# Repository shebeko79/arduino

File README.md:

## Projects description
[Pulmonary Function Testing (PFT)](./pft)

[Car track using telegram bot](./car_dfrobot)

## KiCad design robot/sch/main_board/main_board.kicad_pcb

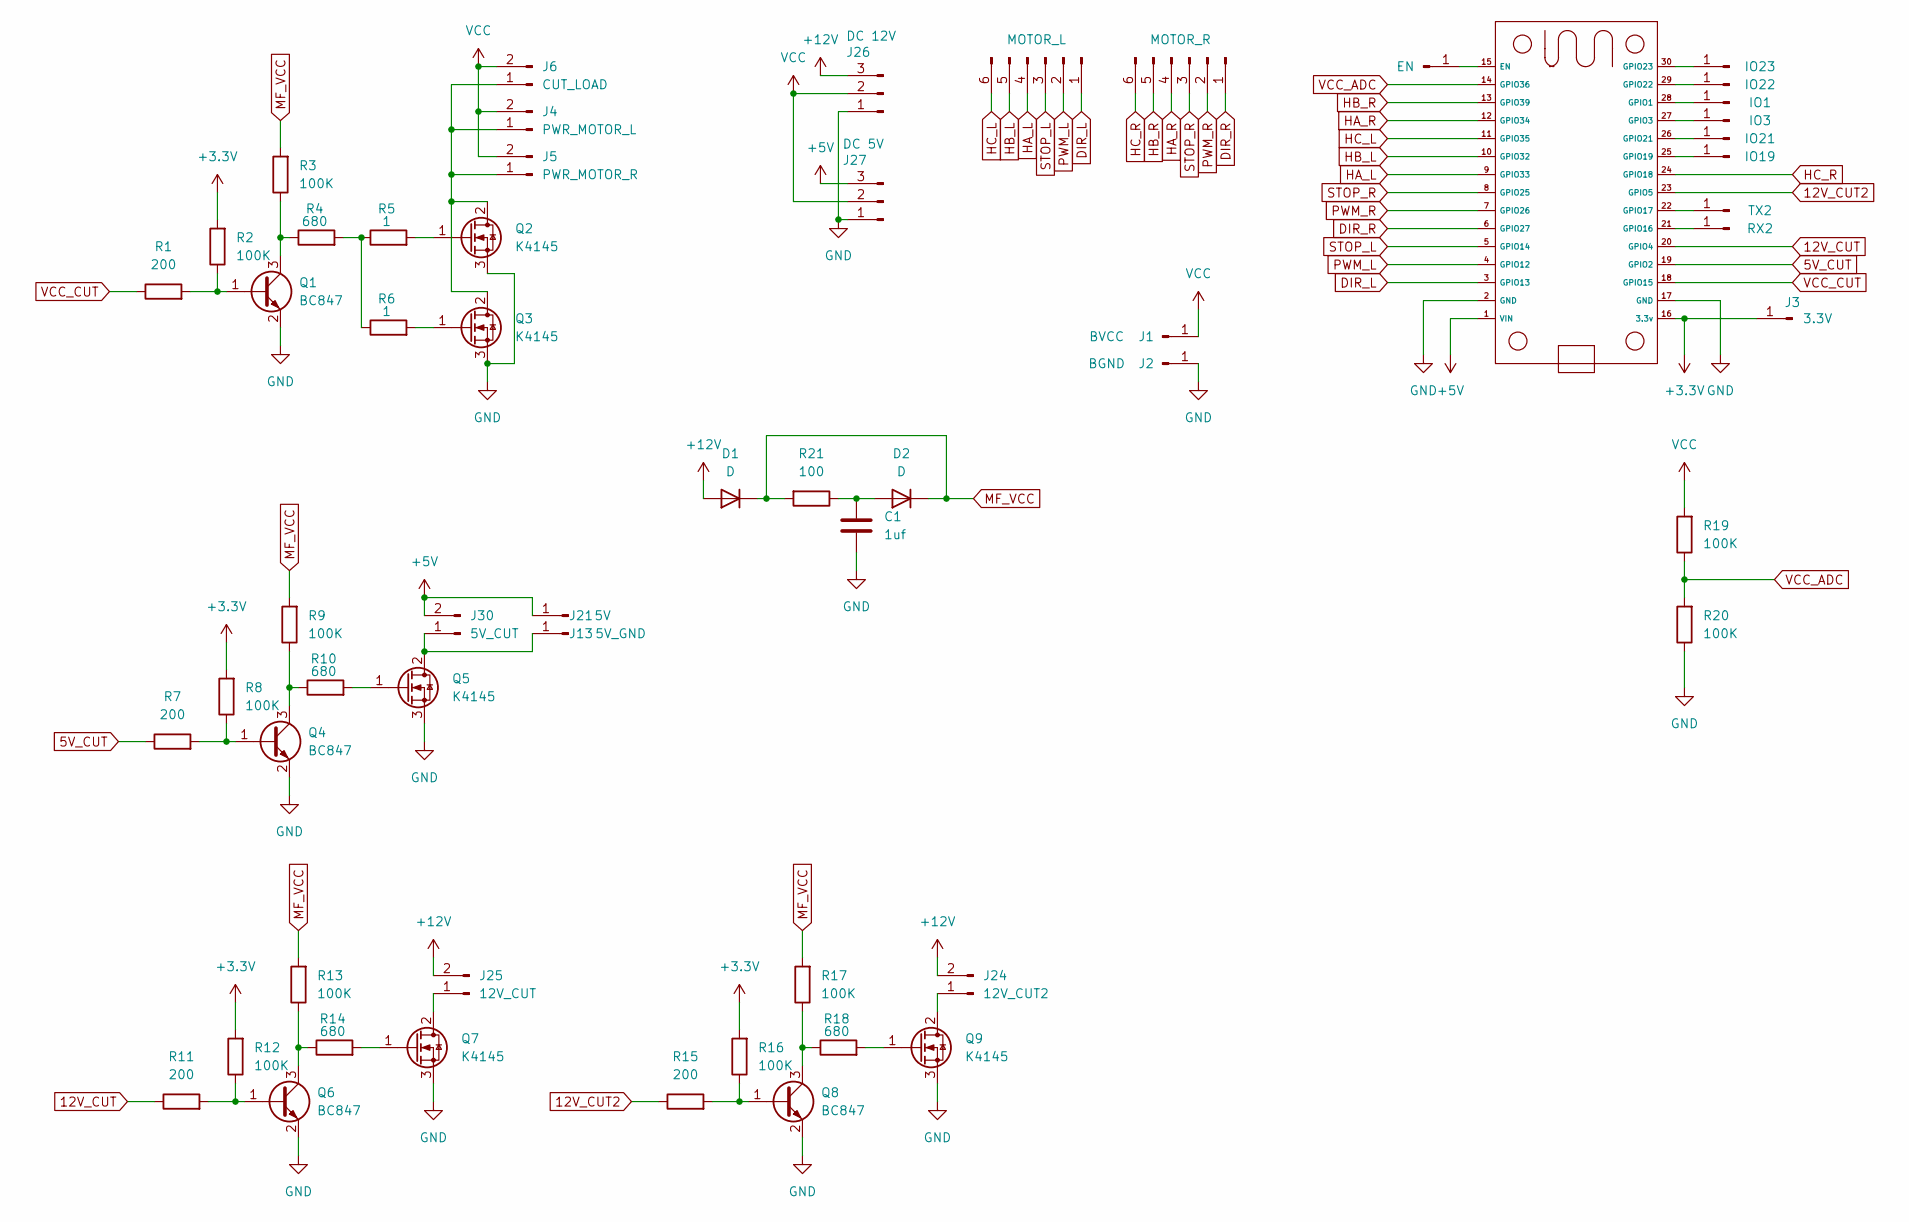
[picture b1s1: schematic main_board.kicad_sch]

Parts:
C1: 1uf; C_0805_2012Metric_Pad1.18x1.45mm_HandSolder
D1, D2: D; D_SMA_Handsoldering
J1: BVCC; SolderWirePad_1x01_SMD_4x8mm
J2: BGND; SolderWirePad_1x01_SMD_4x8mm
J3: 3.3V; SolderWirePad_1x01_SMD_2x4mm
J4: PWR_MOTOR_L; SolderWire-2.5sqmm_1x02_P7.2mm_D2.4mm_OD3.6mm
J5: PWR_MOTOR_R; SolderWire-2.5sqmm_1x02_P7.2mm_D2.4mm_OD3.6mm
J6: CUT_LOAD; SolderWire-2.5sqmm_1x02_P7.2mm_D2.4mm_OD3.6mm
J7: MOTOR_L; JST_XH_B6B-XH-A_1x06_P2.50mm_Vertical
J8: MOTOR_R; JST_XH_B6B-XH-A_1x06_P2.50mm_Vertical
J9: EN; SolderWirePad_1x01_SMD_1.5x3mm
J13: 5V_GND; SolderWirePad_1x01_SMD_2x4mm
J14: IO23; SolderWirePad_1x01_SMD_1.5x3mm
J15: IO22; SolderWirePad_1x01_SMD_1.5x3mm
J16: IO1; SolderWirePad_1x01_SMD_1.5x3mm
J17: IO3; SolderWirePad_1x01_SMD_1.5x3mm
J18: IO21; SolderWirePad_1x01_SMD_1.5x3mm
J19: IO19; SolderWirePad_1x01_SMD_1.5x3mm
J21: 5V; SolderWirePad_1x01_SMD_2x4mm
J22: TX2; SolderWirePad_1x01_SMD_1.5x3mm
J23: RX2; SolderWirePad_1x01_SMD_1.5x3mm
J24: 12V_CUT2; SolderWire-1sqmm_1x02_P5.4mm_D1.4mm_OD2.7mm
J25: 12V_CUT; SolderWire-1sqmm_1x02_P5.4mm_D1.4mm_OD2.7mm
J26: DC 12V; SolderWire-1.5sqmm_1x03_P6mm_D1.7mm_OD3mm
J27: DC 5V; SolderWire-1.5sqmm_1x03_P6mm_D1.7mm_OD3mm
J30: 5V_CUT; SolderWire-1sqmm_1x02_P5.4mm_D1.4mm_OD2.7mm
Q1, Q4, Q6, Q8: BC847; SOT-23
Q2, Q3, Q5, Q7, Q9: K4145; TO-220-3_Vertical
R1, R7, R11, R15: 200; R_0805_2012Metric
R2, R3, R8, R9, R12, R13, R16, R17, R19, R20: 100K; R_0805_2012Metric
R4, R10, R14, R18: 680; R_0805_2012Metric
R5, R6: 1; R_0805_2012Metric
R21: 100; R_0805_2012Metric
U1: ESP32_30pin

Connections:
5V_CUT: R7.1, U1.19 (GPIO2)
12V_CUT: R11.1, U1.20 (GPIO4)
12V_CUT2: R15.1, U1.23 (GPIO5)
+3.3V: J3.1, R2.2, R8.2, R12.2, R16.2, U1.16 (3.3v)
+5V: J21.1, J27.3, J30.2, U1.1 (VIN)
+12V: D1.2 (A), J24.2, J25.2, J26.3
DIR_L: J7.1, U1.3 (GPIO13)
DIR_R: J8.1, U1.6 (GPIO27)
GND: C1.1, J2.1, J26.1, J27.1, Q1.2 (E), Q2.3 (S), Q3.3 (S), Q4.2 (E), Q5.3 (S), Q6.2 (E), Q7.3 (S), Q8.2 (E), Q9.3 (S), R20.1, U1.2 (GND), U1.17 (GND)
HA_L: J7.4, U1.9 (GPIO33)
HA_R: J8.4, U1.12 (GPIO34)
HB_L: J7.5, U1.10 (GPIO32)
HB_R: J8.5, U1.13 (GPIO39)
HC_L: J7.6, U1.11 (GPIO35)
HC_R: J8.6, U1.24 (GPIO18)
MF_VCC: D1.1 (K), D2.1 (K), R3.2, R9.2, R13.2, R17.2, R21.2
unnamed: C1.2, D2.2 (A), R21.1
unnamed: J4.1, J5.1, J6.1, Q2.2 (D), Q3.2 (D)
unnamed: J9.1, U1.15 (EN)
unnamed: J13.1, J30.1, Q5.2 (D)
unnamed: J14.1, U1.30 (GPIO23)
unnamed: J15.1, U1.29 (GPIO22)
unnamed: J16.1, U1.28 (GPIO1)
unnamed: J17.1, U1.27 (GPIO3)
unnamed: J18.1, U1.26 (GPIO21)
unnamed: J19.1, U1.25 (GPIO19)
unnamed: J22.1, U1.22 (GPIO17)
unnamed: J23.1, U1.21 (GPIO16)
unnamed: J24.1, Q9.2 (D)
unnamed: J25.1, Q7.2 (D)
unnamed: Q1.1 (B), R1.2, R2.1
unnamed: Q1.3 (C), R3.1, R4.1
unnamed: Q2.1 (G), R5.2
unnamed: Q3.1 (G), R6.2
unnamed: Q4.1 (B), R7.2, R8.1
unnamed: Q4.3 (C), R9.1, R10.1
unnamed: Q5.1 (G), R10.2
unnamed: Q6.1 (B), R11.2, R12.1
unnamed: Q6.3 (C), R13.1, R14.1
unnamed: Q7.1 (G), R14.2
unnamed: Q8.1 (B), R15.2, R16.1
unnamed: Q8.3 (C), R17.1, R18.1
unnamed: Q9.1 (G), R18.2
unnamed: R4.2, R5.1, R6.1
PWM_L: J7.2, U1.4 (GPIO12)
PWM_R: J8.2, U1.7 (GPIO26)
STOP_L: J7.3, U1.5 (GPIO14)
STOP_R: J8.3, U1.8 (GPIO25)
VCC: J1.1, J4.2, J5.2, J6.2, J26.2, J27.2, R19.2
VCC_ADC: R19.1, R20.2, U1.14 (GPIO36)
VCC_CUT: R1.1, U1.18 (GPIO15)

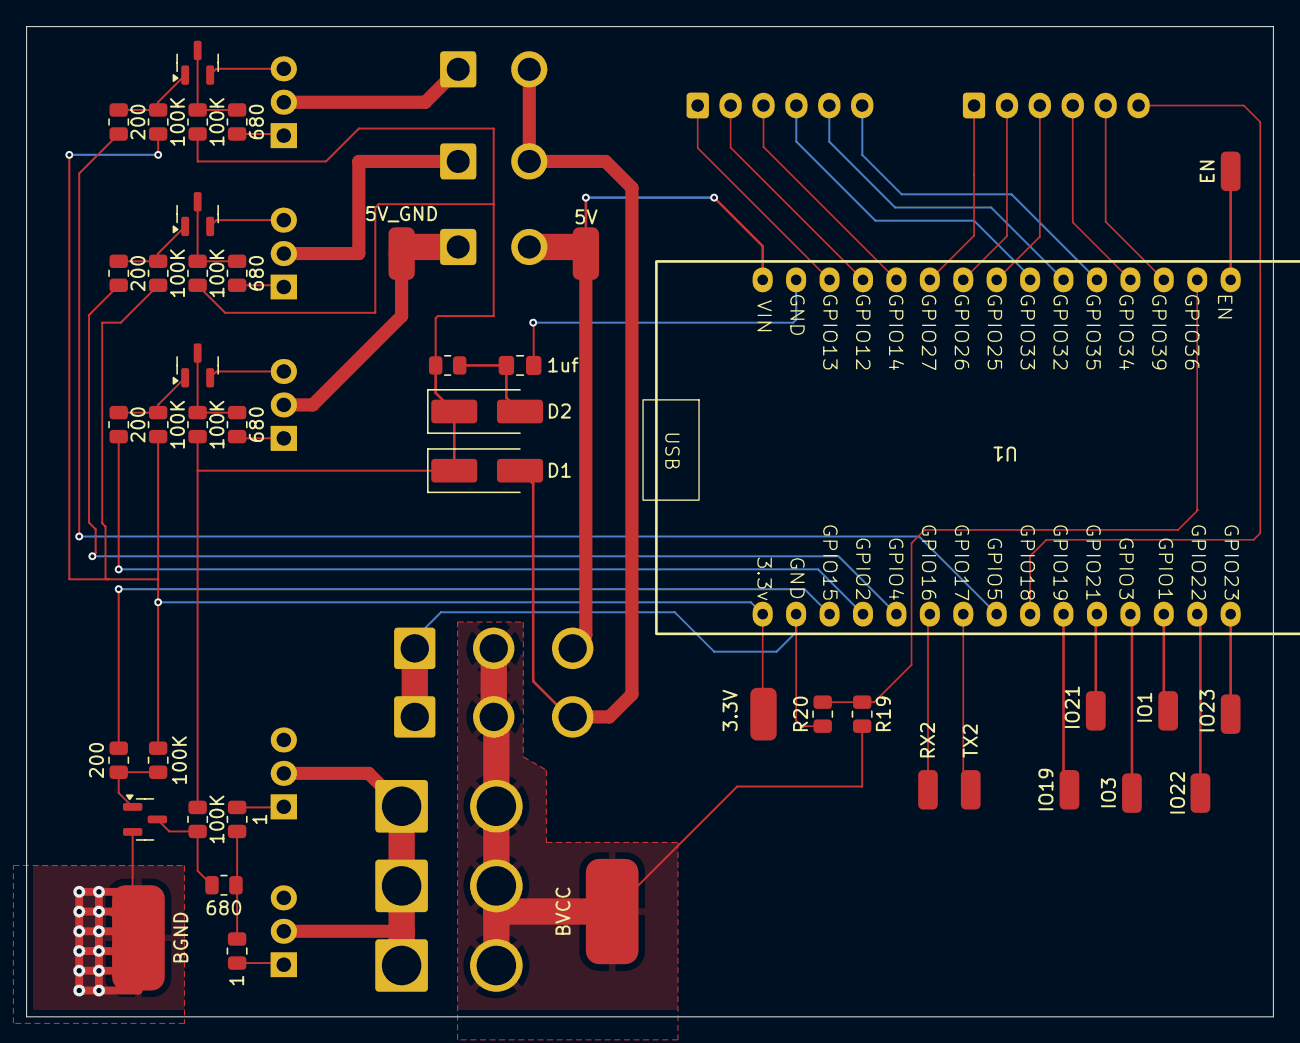
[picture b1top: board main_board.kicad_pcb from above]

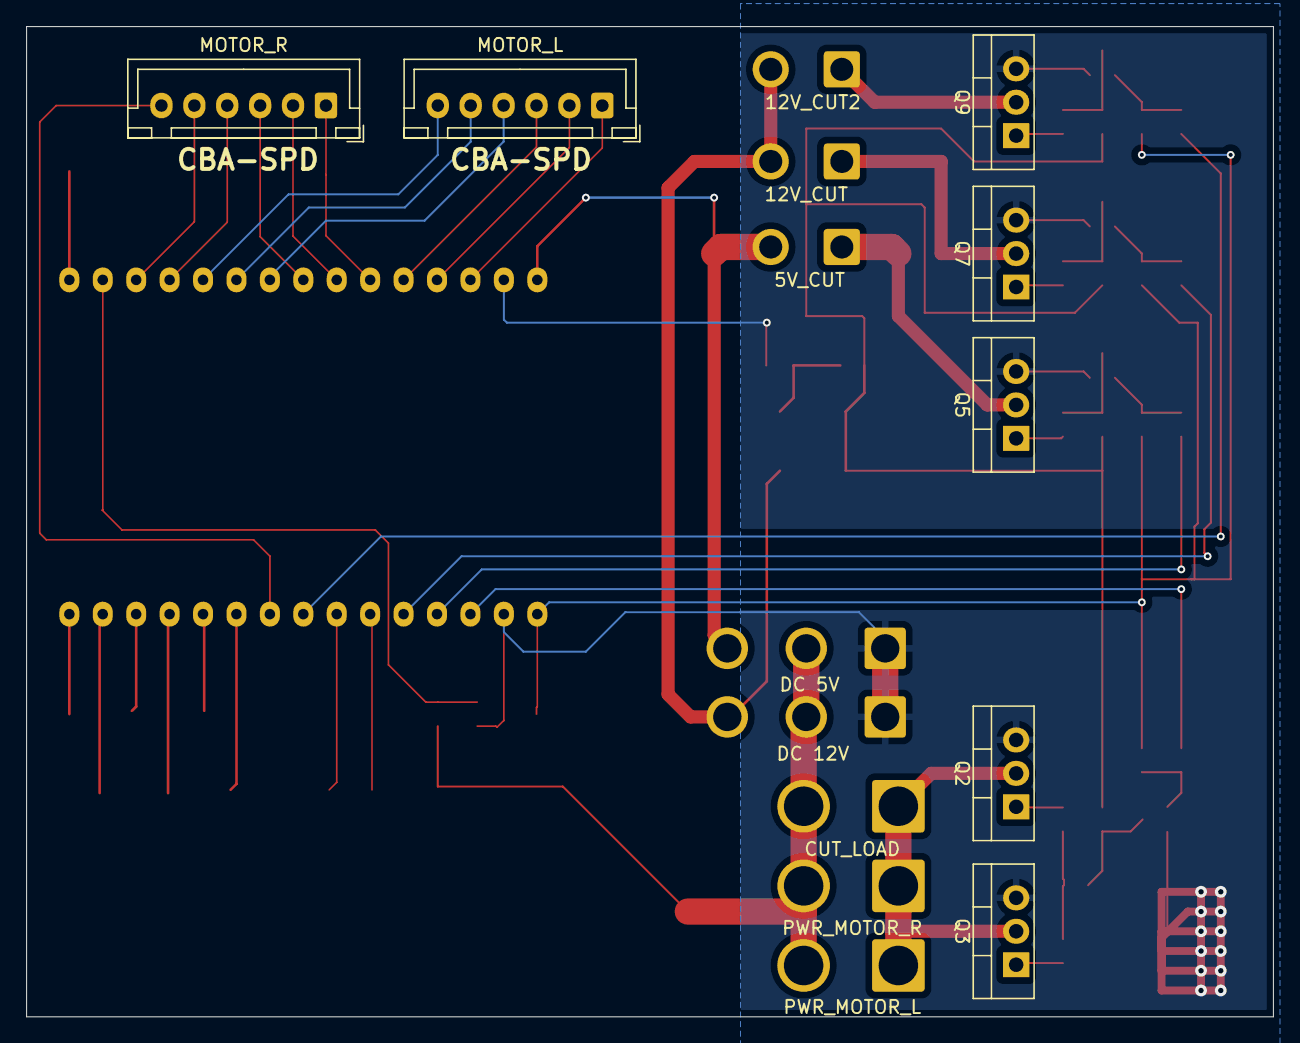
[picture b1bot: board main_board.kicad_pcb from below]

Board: 2 copper layers, 94.8 x 75.2 mm, 58 parts (15 on the bottom side), 51 nets.

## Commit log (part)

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2021-11-11 add chicken
2021-11-11 add tests
2021-11-11 add doc
2021-11-11 add dachagaraz
2021-11-11 commit others projects
2021-11-11 CmAlarm
2021-12-26 Recover after WiFi failures. Silent messages. Temp sensor temporary doesn't work
2021-12-26 gitignore
2021-12-26 wire_length
2021-12-26 change for esp32
2021-12-26 udp_client
2023-01-16 Add scheme of uno sim800 board
2023-01-17 Files w/o secret keys
2023-02-15 SIM7000 car tracking version
2023-02-15 less debug information
2023-02-15 Just AT command list. Useful for troubleshooting.
2024-03-22 Pulmonary function tests
2024-03-22 Better touch screen interraction Better graph
2024-03-23 ticks[] calculated just in timer scale chart to actual data print seconds in x axis
2024-04-11 Draw battery status
2024-04-11 Add 3d model
2024-04-13 1. Result number on a different screen. 2. Add sleep mode. Sleep mode note that effective, device still consume 8mA so we still need physical power button
2024-04-13 1. Reduce mundshtuk size 2. Add cover to hide electronics
2024-04-13 Add *.blend1 to gitignore
2024-04-13 1. Move tick counter from timer isr to pin isr 2. Reduce scale because free spin was physically removed 3. Shortest scale must be not shorter than 1 second
2024-04-19 Draw total air-flow Draw FVC,FEV1,FEV1/FVC in the results
2024-04-20 Add license and readme
2024-04-20 Add references
2024-04-20 Fix spelling in README.md
2024-04-20 Add demo video to README.md
2024-04-20 Images of device
2024-04-20 Reduce images size
2024-04-20 Add images to README.md
2024-08-30 2 wheel platform based on esp32
2024-09-11 SIM7070 documentation
2024-09-11 Use macro for telegram chat id
2024-09-11 Test sim7070 AT commands sequence
2024-09-11 1. Save certificate into modem 2. Just regular AT terminal
2024-09-11 Prepare for modem replacement Isolate modem header
2024-09-11 Add sim7070.h
2024-09-13 Same speed as debug in car_dfrobot
2024-09-13 Remove comments
2024-09-13 1. Use F() macro to store strings in PROGMEM 2. Rewrite for HTTPS. Still need to debug.
2024-09-13 GPS can't work at the same time with mobile network. See https://stackoverflow.com/questions/61857667/sim7080g-module-cant-send-data-over-tcp-while-using-gnss
    That's why we must switch off GPS and then send data.
    For the same reason we can't keep HTTPS connection and have to open it again for each request.
2024-09-13 1. Read receive buffer chunk-by-chunk 2. use separate buffer for telegram, because modem_answer overrides by commands 3. Push 2 message at start, because first lost anyway 4. Commented out unnecessar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
2024-09-15 Overall projects readme
2024-09-20 Bluetooth remote control
2024-09-28 Add "block" command in BT remote control
2024-09-28 Examples files for maixcam
2024-10-05 Implementing state machine for UI
2024-10-06 Implement button click and rectangle selection
2024-10-06 Add rectangle normalization
2024-10-07 Add MoveTo algo.
2024-10-12 returns image each second on web
2024-10-12 Add buttons using ChatGPT
2024-10-12 ChatGPT button click handler
2024-10-12 chatGPT image click
2024-10-12 chatGPT select rectangle
2024-10-12 1. Prevent rectangle visible until object selection (chatGPT) 2. Prevent dragging image (chatGPT) 3. Process requests on server side 4. Prevent crash, when to_jpeg() returns None after script restart
2024-10-12 Add just move states
2024-10-13 Mobile adaptation for select rectangle (chatGPT)
2024-10-13 Click on image for mobile (chatGPT)
2024-10-13 Move buttons to right
2024-10-13 Rename move states for vertical alignment Load main html from BASE_PATH path
2024-10-15 Add WiFi features. If fail connect to WiFi switch to AP mode
2024-10-16 Disable wifi switch AP mode doesn't start DHCP And switch back to STA go wrong.
2024-10-19 Configuring network thru python was bad idea. Add S30wifidyn which try establish sta connection, if fails switch to ap mode
2024-10-19 Shrink move state to fit on a screen More robust S81robot stop function
2024-10-27 1. Get rid of Flask, because it creates a lot of threads and to noisy 2. Implement synchronized function call in main thread. 3. Get state just after click,click_point, sel_rect requests
2024-10-27 1. Apply immediately /click /click_point /sel_rect to buttons state 2. Return state even if requests are not executed 3. Move server to 80 port
2024-11-09 Increase line width to avoid red-grey rectangles
2024-11-19 pan\tilt stl model
2024-12-08 Parts schematic
2024-12-08 Test of zs-x11h controller
2024-12-09 rename motor.h to mdd3a controller which was used to control dc motor
2024-12-09 Add szx11h motor controller
2024-12-10 1. Move to PlatformIO 2. Speed measurement
2024-12-11 Connect brake pin
2024-12-12 Add PID control
2024-12-12 Change remote to relative protocol
2024-12-12 Add relative protocol
2024-12-13 1. Always brake for zero speed 2. 20kHz PWM just follow controllers recommendations 3. Separate RELATIVE_MAX_SPEED because it a bit scary with full speed 4. Dump wheels state in com port to have a gl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
2024-12-13 command to set maximum relative_speed
2024-12-13 Better command parsing
2024-12-21 Update 3d models 1. Base for pantilt 2. Cover for 2020 profile
2024-12-21 shorter screw placeholer
2024-12-25 Move servo closer to the front
2024-12-25 Maixcam pinout
2024-12-28 Fix rotation cast
2024-12-28 Change mover to speed and pan
2024-12-31 Add scservo_sdk and pan_tilt example proba/pan_tilt.py all necessary function (i.e. reduce baud rate) which performes thru USB of SCServo controller maix/pan_tilt.py is a sketch for pan-til support
2025-01-01 Implementation of pan-tilt tracking Doesn't work as expected yet
2025-01-01 Add exit state for graceful exit
2025-01-02 Release servos when exit Measure real focus distance
2025-01-04 Full screen image
2025-01-05 1. Use relative (0.0-1.0) image coordinates for tracker 2. Make image full-screen on http page
2025-01-07 1. Increase camera resolution 2. Add keyboard support to control camera and movement 3. Add Pan state for mobile
2025-01-27 rtsp test
2025-01-27 Avoid low power exception on shutdown
2025-01-27 send file feature Potentially unsafe we need to check if file really in assets directory
2025-02-16 PID control on pwm instead of speed
2025-02-16 Split motor_speed.h to .cpp and .h
2025-02-16 Try to make remote more stable
2025-02-16 Assume we have some koef. between PWM and unloaded wheel speed. Make error correction around this value. Also introduced delays. But it doesn't look like it helps somehow. Add maximum acceleration bu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
2025-02-16 Motors control in separate thread
2025-03-08 Speed test with different masses and PWM
2025-03-13 Yet another speed control. Based on equilibrium velocity. Still not satisfied how it's work
2025-03-14 Temoprary checkpoint
2025-03-15 Less or more satisfied. Works pretty much the same for different loads. Like empty truck or me as a load. We don't try to adjust m_speed2pwm because it not constant even for the same environment. In 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
    The general idea now is:
    - adjust PWM slowly unless it increase the speed with any acceleration
    - add one time kick to PWM if speed remain zero
    - break if speed go to far in wrong direction or go with acceleration
2025-03-22 rename timer0 to speed_timer
2025-03-22 Increase pan/tilt insensitive zone to avoid shaking
2025-03-30 Yolo custom model track
2025-04-19 Hide internal tracker structure
2025-04-19 Implement yolo trackers
2025-04-21 Add pan, move, follow tracking modes.
2025-04-21 Caption for tracker selection
2025-04-21 Rename room to yolo
2025-04-21 Show click caption and rectangle caption in HTML
2025-04-21 Fix X offset in point and rectangle selection. Wrong condition cause default 640X480 doesn't update to real size 640X640
2025-04-21 Fix nanotrack display on the screen
2025-04-23 1. Pass correct fit to MoveTo 2. Ensure tracker still in the yolo_trackers, because self stopping algo calls YoloTrackObject::stop() 2 times.
2025-09-29 Test of MOSFET switch
2025-09-29 Discover different streaming options
2025-09-29 Kikad board of the robot
2025-09-29 Moved to https://github.com/shebeko79/robocart.git
2025-10-12 Test of speed and accuracy of ESP ADC
2025-11-29 Few tests
2026-05-07 Moved to robocart project
